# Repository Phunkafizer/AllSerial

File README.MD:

# AllSerial
## An universal sophisticated USB-serial converter

SEE PROJECTHOMEPAGE UNDER [https://www.seegel-systeme.de/2025/07/10/allserial](https://www.seegel-systeme.de/2025/07/10/allserial)

Over the course of time I had to work with many different devices which had to be connected via a kind of serial interface. There are lots of different cheap USB-serial adapters available, but no adapter was including all features I needed in a single device. Every USB-serial adapter has in common the USB Controller. So I came up with the idea having a masterboard providing all the common features like USB interface, isolation and diagnostic elements. The most used interfaces (RS232, RS485, TTL UART, TTY current loop & LIN) are build up on slave modules which can be plugged into the mainboard. If a custom interface is needed, there is an KiCad library available making it easy to create one by yourself. 

## Features
- Open source
- Isolated
- Reset button for reenumerating device on the USB
- Status LEDs (RX, TX, Power, TXEN)
- modular, just exchange daughterboard for different interfaces
- RS232 completley connected (RXD, TXD, RTS, CTS, DTR, DSR, RI, DCD)
- RS485, RS422 with Handshake
- TTY current loop 4/3/2 wire active/passive
- LIN
- TTL 1.8/2.5/3.3/5 V
- KiCad library for easily creating custom modules

## Modules (tested & working)
* Mainboard FT232

* RS 422/485 

* RS 232 

* TTL 

* TTY current loop 

* LIN 

* 1wire (with DS2480B) 

* Programmer for ESP8266 (auto reset&boot) 

## Modules (under development)
* Mainboard with ESP32-S3 for accessing slave modules via USB, WiFi & Bluetooth 

* mBus master
* Digi XBee radiomodem 

* eBus 

## Software
* [hterm](http://www.der-hammer.info/terminal/) (windows)
* [putty](https://www.chiark.greenend.org.uk/~sgtatham/putty/latest.html) (windows/unix)

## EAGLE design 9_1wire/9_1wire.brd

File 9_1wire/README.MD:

# 9 1wire
provides a 1-wire interface

* using IC DS2480B
* provides 12 V for programming 1wire eeproms

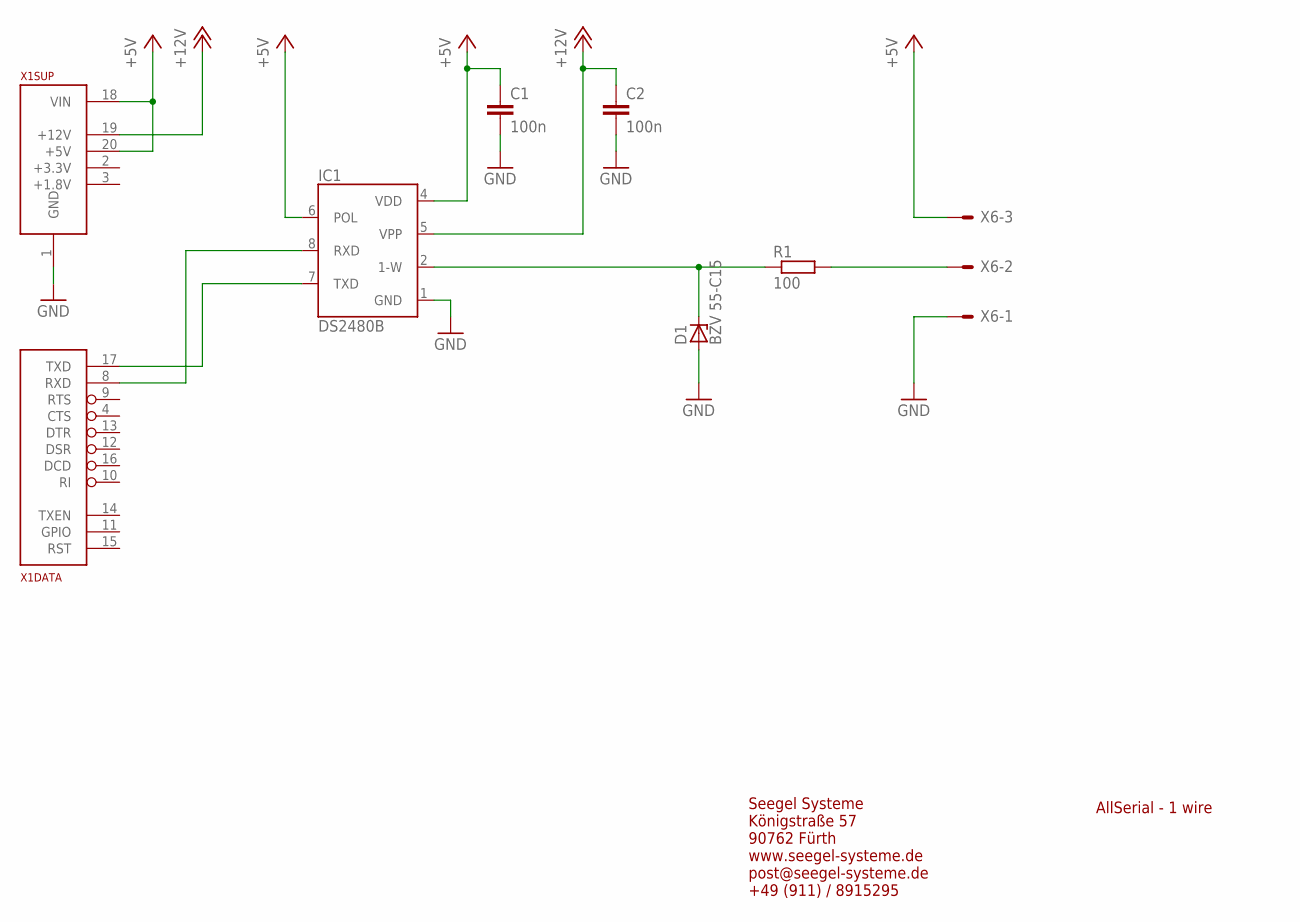
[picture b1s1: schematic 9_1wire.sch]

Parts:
C1, C2: 100n; C0805
D1: BZV 55-C15; SOD80C
IC1: DS2480B; SO08
R1: 100; R0805
X1: ALLSERIALSLAVE; DAUGHTER-THT
X6: AKL18X-03W; AKL182-03

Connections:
+5V: C1.1, IC1.4 (VDD), IC1.6 (POL), X1.18 (VIN), X1.20 (+5V), X6.P$3
+12V: C2.1, IC1.5 (VPP), X1.19 (+12V)
GND: C1.2, C2.2, D1.A, IC1.1 (GND), X1.1 (GND), X6.P$1
unnamed: IC1.7 (TXD), X1.17 (TXD)
unnamed: IC1.8 (RXD), X1.8 (RXD)
unnamed: D1.C, IC1.2 (1-W), R1.1
unnamed: R1.2, X6.P$2

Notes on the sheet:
AllSerial - 1 wire
Seegel Systeme Königstraße 57 90762 Fürth www.seegel-systeme.de post@seegel-systeme.de +49 (911) / 8915295

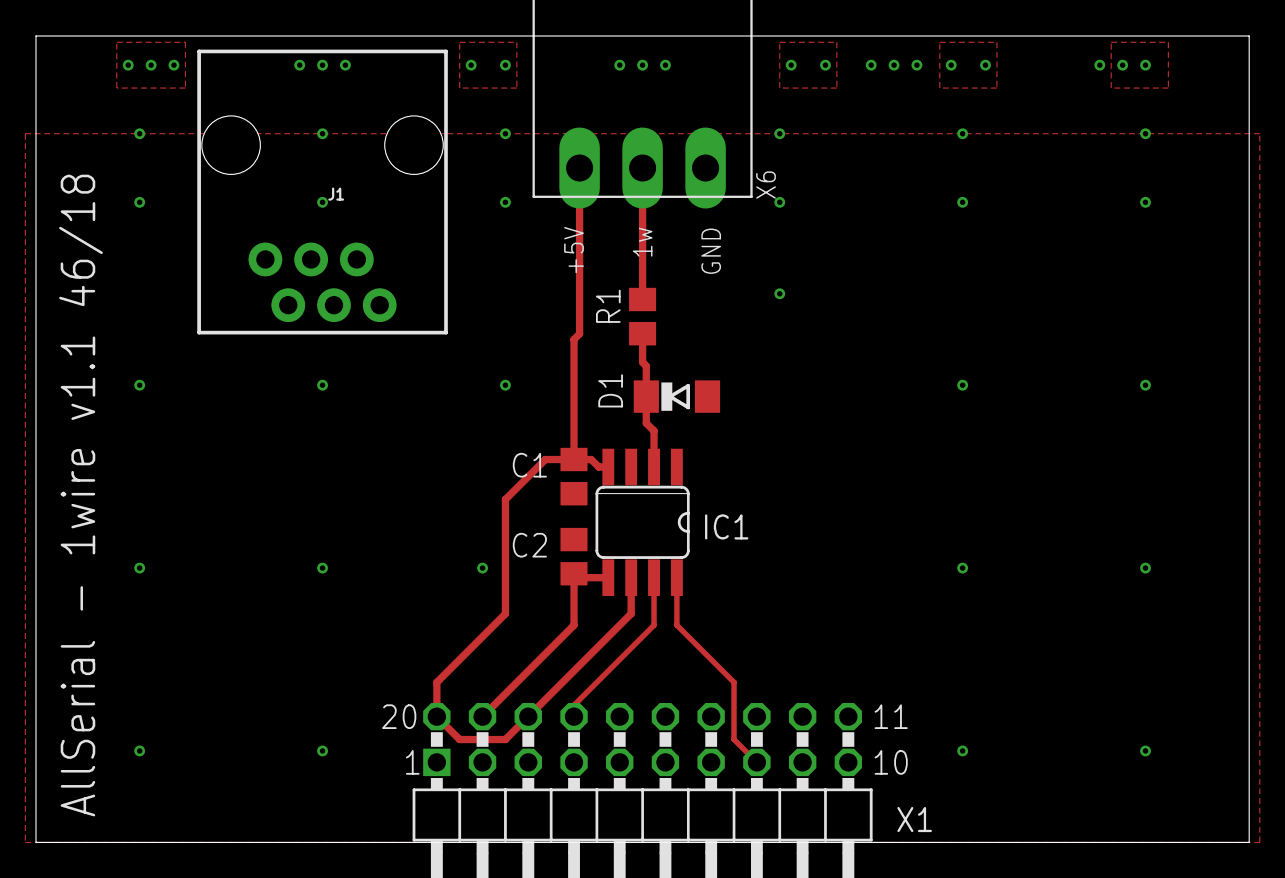
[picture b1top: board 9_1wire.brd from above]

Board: 2 copper layers, 67.4 x 44.8 mm, 8 parts (0 on the bottom side), 7 nets.

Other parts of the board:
J1: RJ11; RJ11-6

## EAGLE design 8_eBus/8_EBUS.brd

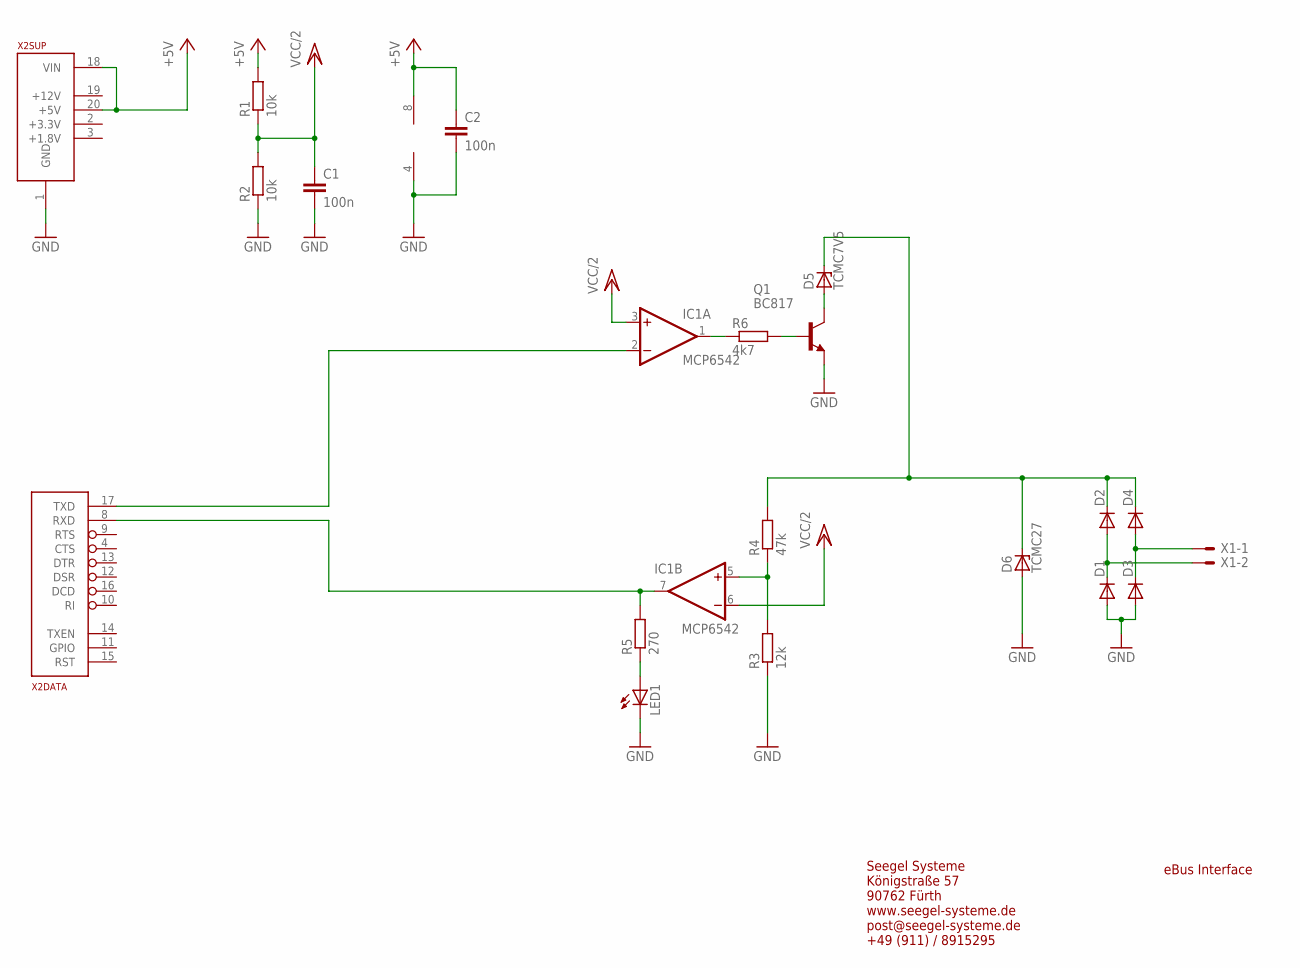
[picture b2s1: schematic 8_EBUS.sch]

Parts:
C1, C2: 100n; C0805
D1, D2, D3, D4: DIODE-SOD80C; SOD80C
D5: TCMC7V5; SOD80C
D6: TCMC27; SOD80C
IC1: MCP6542; SO08
LED1: LEDCHIPLED_0805; CHIPLED_0805
Q1: BC817; SOT23-BEC
R1, R2: 10k; R0805
R3: 12k; R0805
R4: 47k; R0805
R5: 270; R0805
R6: 4k7; R0805
X1: AKL18X-02W; AKL182-02
X2: ALLSERIALSLAVE; DAUGHTER-THT

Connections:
+5V: C2.1, IC1.8 (V+), R1.2, X2.18 (VIN), X2.20 (+5V)
GND: C1.2, C2.2, D1.A, D3.A, D6.A, IC1.4 (V-), LED1.C, Q1.E, R2.1, R3.1, X2.1 (GND)
unnamed: D2.C, D4.C, D5.C, D6.C, R4.2
unnamed: D3.C, D4.A, X1.P$1
unnamed: D1.C, D2.A, X1.P$2
unnamed: Q1.B, R6.2
unnamed: D5.A, Q1.C
unnamed: IC1.5 (+IN), R3.2, R4.1
unnamed: IC1.2 (-IN), X2.17 (TXD)
unnamed: IC1.1 (OUT), R6.1
unnamed: LED1.A, R5.1
unnamed: IC1.7 (OUT), R5.2, X2.8 (RXD)
VCC/2: C1.1, IC1.3 (+IN), IC1.6 (-IN), R1.1, R2.2

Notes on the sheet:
eBus Interface
Seegel Systeme Königstraße 57 90762 Fürth www.seegel-systeme.de post@seegel-systeme.de +49 (911) / 8915295

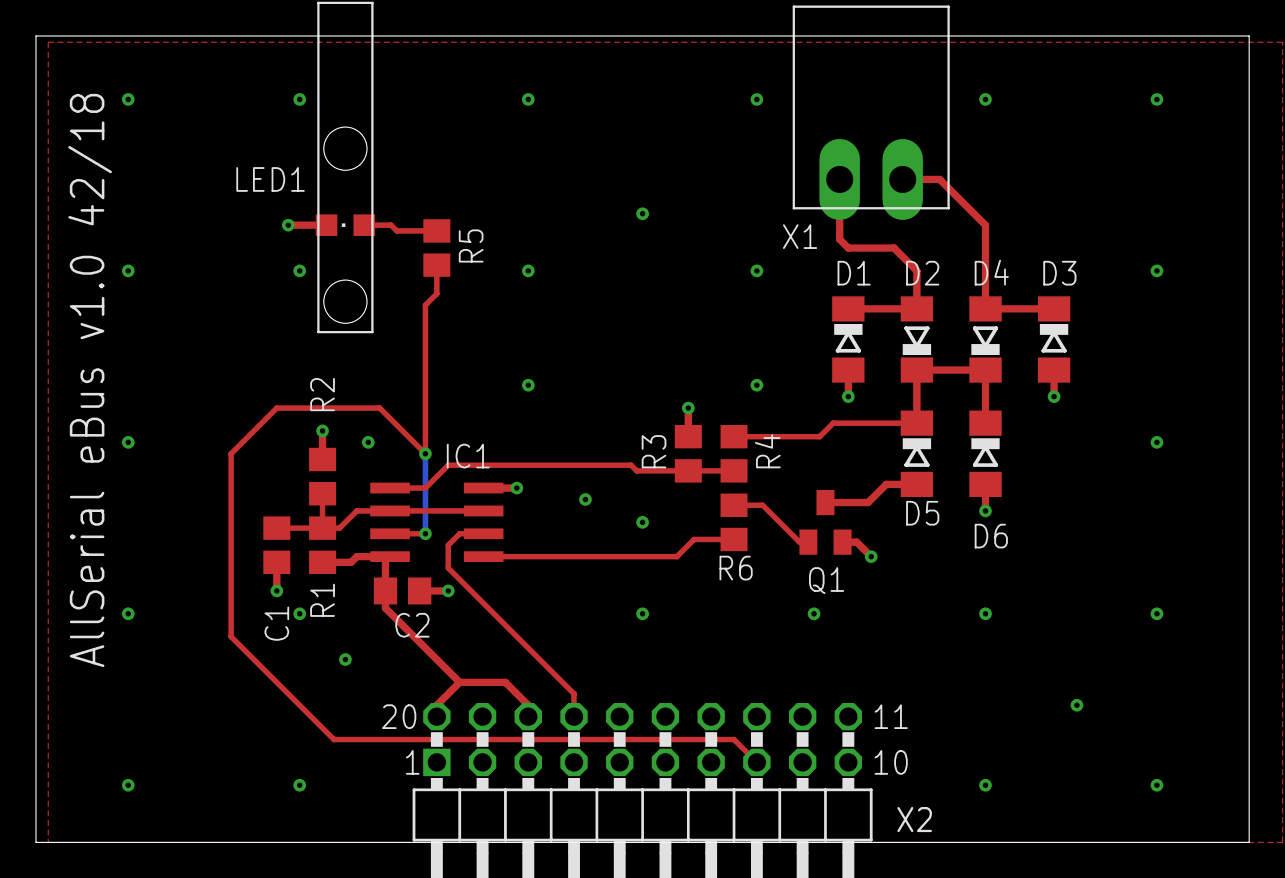
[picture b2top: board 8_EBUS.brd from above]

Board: 2 copper layers, 67.4 x 44.8 mm, 20 parts (0 on the bottom side), 13 nets.

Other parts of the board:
U$1: 1271.1000

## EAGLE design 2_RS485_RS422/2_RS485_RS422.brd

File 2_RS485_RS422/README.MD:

# AllSerial RS 422/485 module
Provides a RS 485/422 interface

* Jumper for termination
* Additional doublepair for RS422 with handshake lines
* RTS/DTR CTS/DSR for handshake can be select with jumper

Reichelt Warenkorb: https://www.reichelt.de/my/1489968

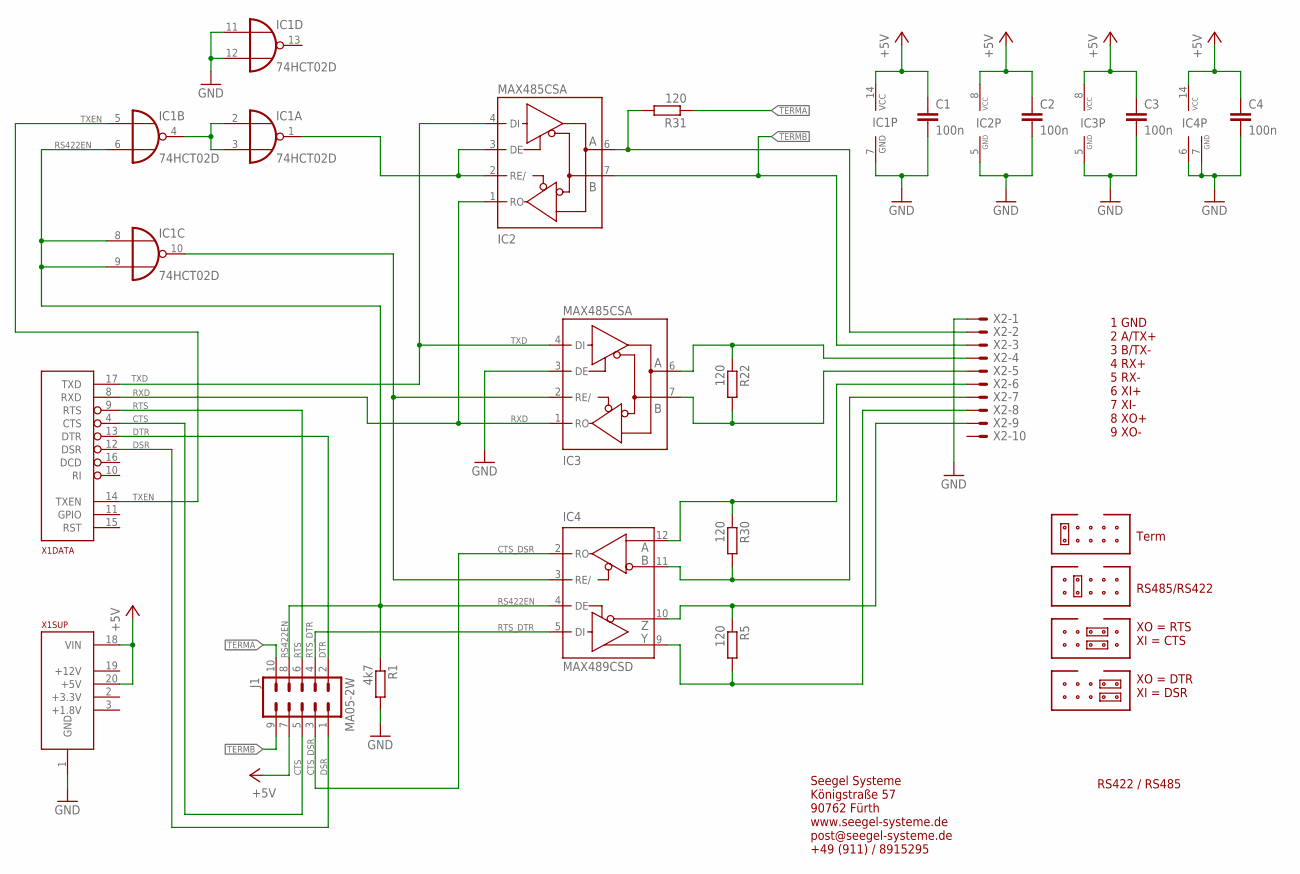
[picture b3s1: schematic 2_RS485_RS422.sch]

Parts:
C1, C2, C3, C4: 100n; C0805
IC1: 74HCT02D; SO14
IC2, IC3: MAX485CSA; SO08
IC4: MAX489CSD; SO14
J1: MA05-2W
R1: 4k7; R0805
R5, R22, R30, R31: 120; R0805
X1: ALLSERIALSLAVE; DAUGHTER-THT
X2: AKL18X-10W; AKL182-10

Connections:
+5V: C1.1, C2.1, C3.1, C4.1, IC1.14 (VCC), IC2.8 (VCC), IC3.8 (VCC), IC4.14 (VCC), J1.7, X1.18 (VIN), X1.20 (+5V)
CTS: J1.5, X1.4 (CTS)
CTS_DSR: IC4.2 (RO), J1.3
DSR: J1.1, X1.12 (DSR)
DTR: J1.2, X1.13 (DTR)
GND: C1.2, C2.2, C3.2, C4.2, IC1.7 (GND), IC1.11 (I0), IC1.12 (I1), IC2.5 (GND), IC3.3 (DE), IC3.5 (GND), IC4.6 (GND), IC4.7 (GND), R1.2, X1.1 (GND), X2.P$1
unnamed: IC4.11 (B), R30.2, X2.P$7
unnamed: IC4.10 (Z), R5.1, X2.P$9
unnamed: IC2.6 (A), R31.2, X2.P$2
unnamed: IC4.9 (Y), R5.2, X2.P$8
unnamed: IC4.12 (A), R30.1, X2.P$6
unnamed: IC3.7 (B), R22.2, X2.P$5
unnamed: IC3.6 (A), R22.1, X2.P$4
unnamed: IC1.2 (I0), IC1.3 (I1), IC1.4 (O)
unnamed: IC1.1 (O), IC2.2 (RE/), IC2.3 (DE)
unnamed: IC1.10 (O), IC3.2 (RE/), IC4.3 (RE/)
RS422EN: IC1.6 (I1), IC1.8 (I0), IC1.9 (I1), IC4.4 (DE), J1.8, R1.1
RTS: J1.6, X1.9 (RTS)
RTS_DTR: IC4.5 (DI), J1.4
RXD: IC2.1 (RO), IC3.1 (RO), X1.8 (RXD)
TERMA: J1.10, R31.1
TERMB: IC2.7 (B), J1.9, X2.P$3
TXD: IC2.4 (DI), IC3.4 (DI), X1.17 (TXD)
TXEN: IC1.5 (I0), X1.14 (TXEN)

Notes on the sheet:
Seegel Systeme Königstraße 57 90762 Fürth www.seegel-systeme.de post@seegel-systeme.de +49 (911) / 8915295
RS422 / RS485
Term
RS485/RS422
XO = RTS XI = CTS
XO = DTR XI = DSR
1 GND 2 A/TX+ 3 B/TX- 4 RX+ 5 RX- 6 XI+ 7 XI- 8 XO+ 9 XO-

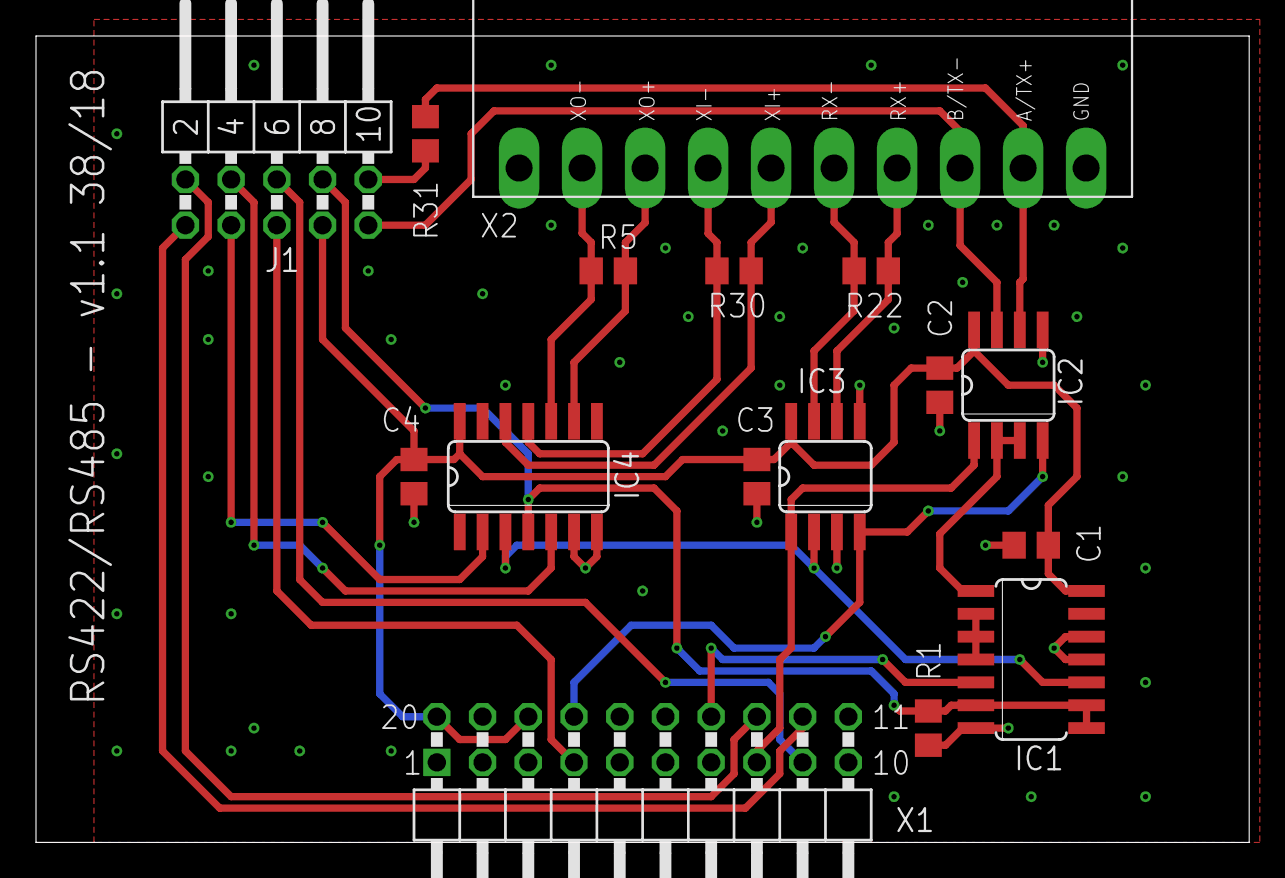
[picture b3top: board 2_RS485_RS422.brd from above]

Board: 2 copper layers, 67.4 x 44.8 mm, 18 parts (0 on the bottom side), 24 nets.

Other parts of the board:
U$4, U$5: JUMPER

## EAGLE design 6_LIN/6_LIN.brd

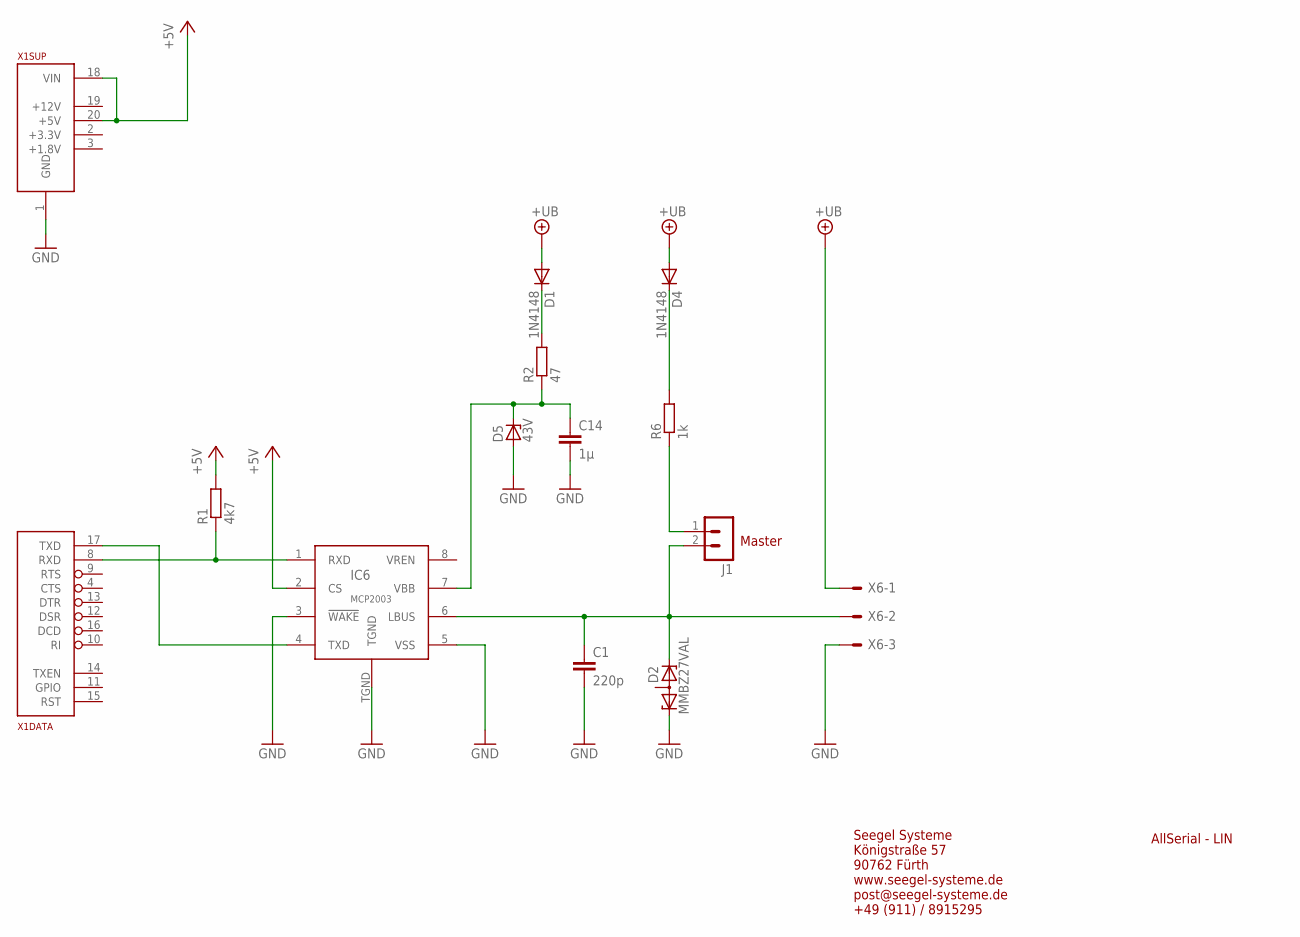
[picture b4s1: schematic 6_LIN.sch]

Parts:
C1: 220p; C0805
C14: 1µ; C0805
D1, D4: 1N4148; MINIMELF
D2: MMBZ27VAL; SOT23
D5: 43V; SOD80C
IC6: MCP2003; SOIC8T
J1: MA02-1W; MA02-W
R1: 4k7; R0805
R2: 47; R0805
R6: 1k; R0805
X1: ALLSERIALSLAVE; DAUGHTER-THT
X6: AKL18X-03W; AKL182-03

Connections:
+5V: IC6.2 (CS), R1.2, X1.18 (VIN), X1.20 (+5V)
+UB: D1.A, D4.A, X6.P$1
GND: C1.2, C14.2, D2.1 (K1), D5.A, IC6.3 (!WAKE), IC6.5 (VSS), IC6.TGND, X1.1 (GND), X6.P$3
unnamed: D1.C, R2.2
unnamed: D4.C, R6.2
unnamed: C14.1, D5.C, IC6.7 (VBB), R2.1
unnamed: C1.1, D2.2 (K2), IC6.6 (LBUS), J1.2, X6.P$2
unnamed: J1.1, R6.1
unnamed: IC6.4 (TXD), X1.17 (TXD)
unnamed: IC6.1 (RXD), R1.1, X1.8 (RXD)

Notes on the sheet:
AllSerial - LIN
Master
Seegel Systeme Königstraße 57 90762 Fürth www.seegel-systeme.de post@seegel-systeme.de +49 (911) / 8915295

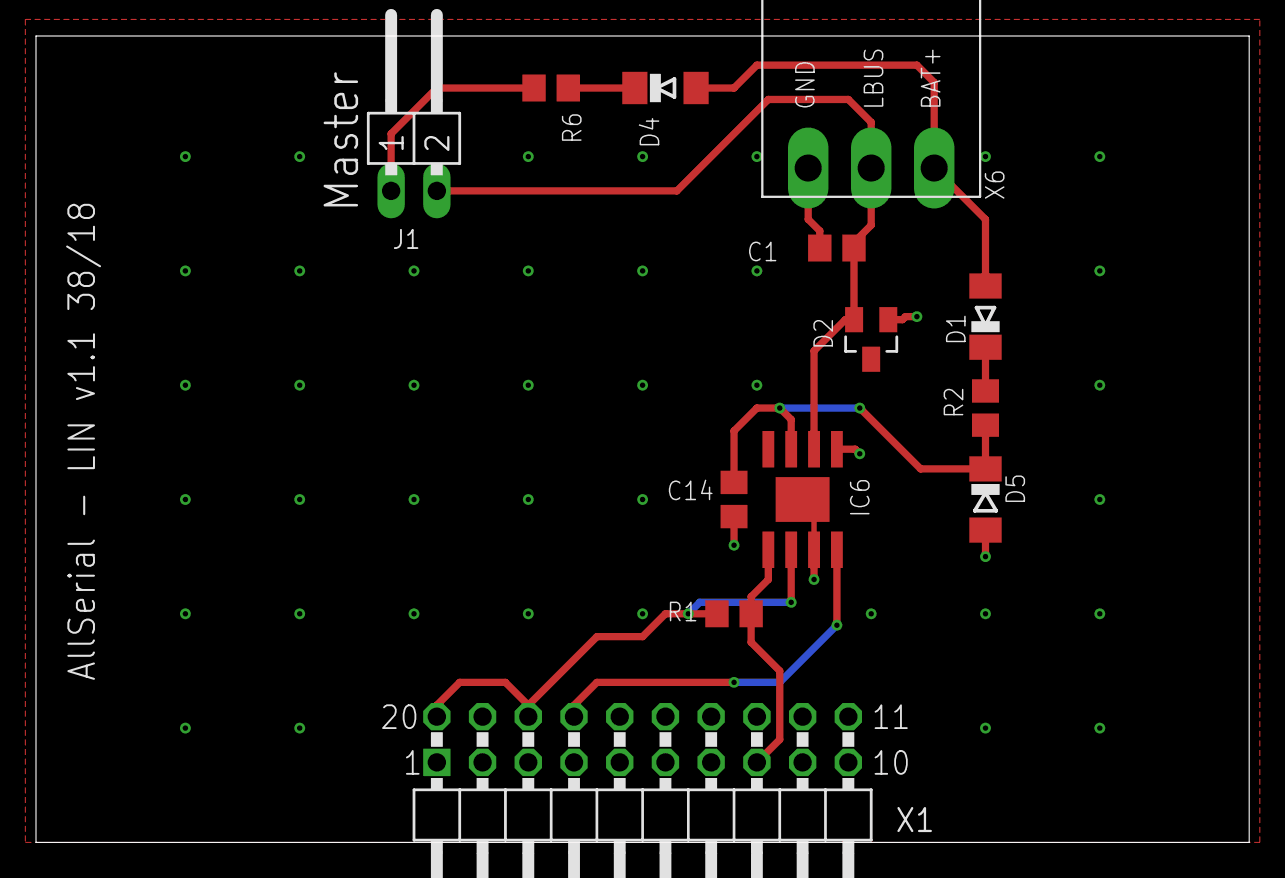
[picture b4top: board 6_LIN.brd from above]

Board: 2 copper layers, 67.4 x 44.8 mm, 13 parts (0 on the bottom side), 10 nets.

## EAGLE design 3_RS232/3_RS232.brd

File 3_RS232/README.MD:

# RS232
Provides a RS 422 interface (DTE)

* fully connected (TX, RX, RTS, CTS, DTR, DSR, RI, DCD)
* 9 pin D-SUB male connector

Reichelt Warenkorb: https://www.reichelt.de/my/1490023

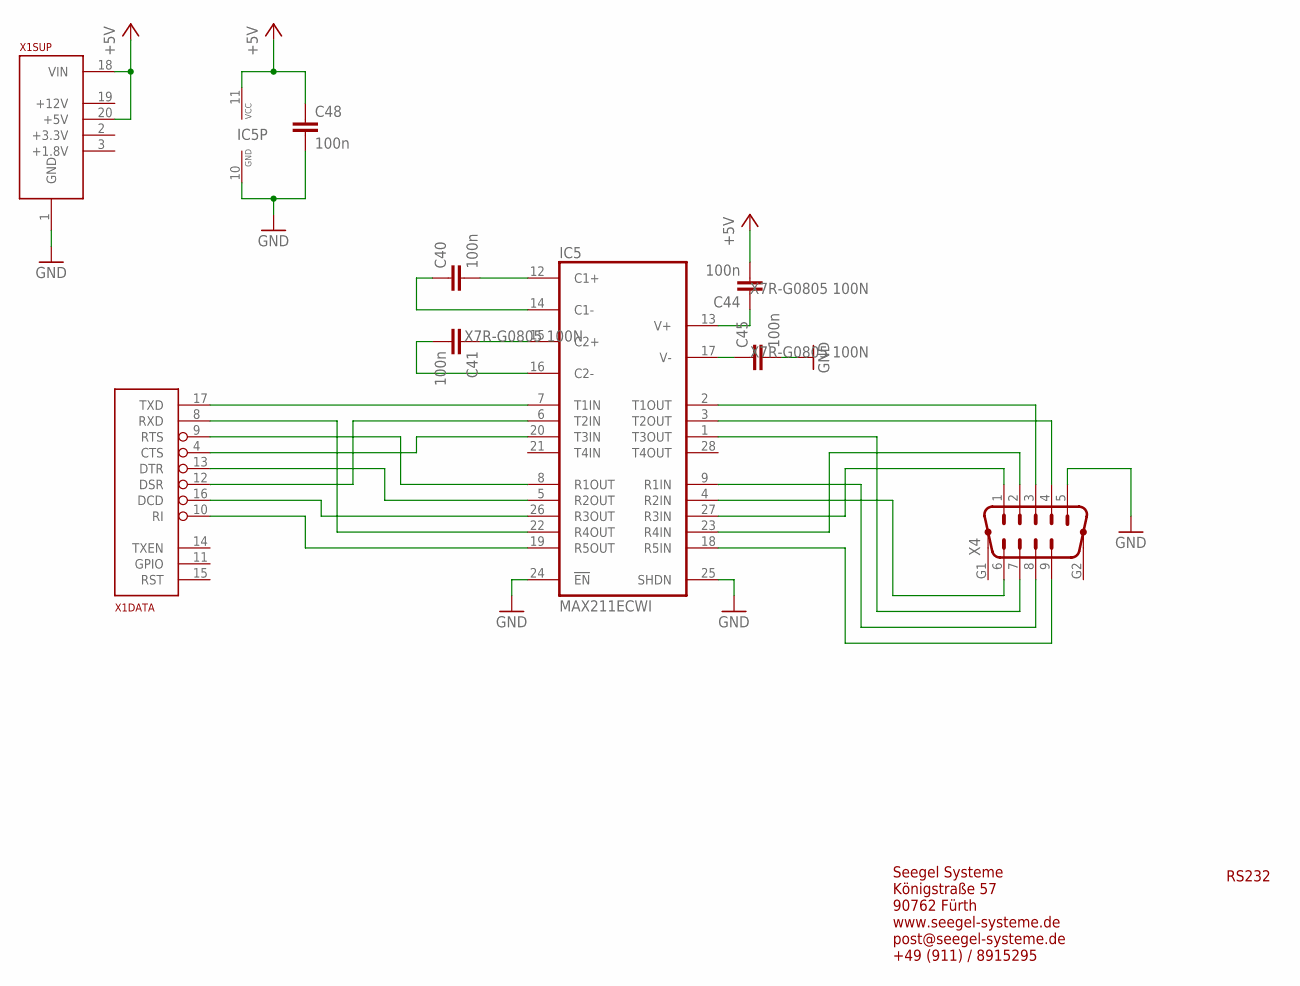
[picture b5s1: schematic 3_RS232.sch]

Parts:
C40, C41, C44, C45, C48: 100n; C0805
IC5: MAX211ECWI; SO28L
X1: ALLSERIALSLAVE; DAUGHTER-THT
X4: M09HP

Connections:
+5V: C44.2, C48.1, IC5.11 (VCC), X1.18 (VIN), X1.20 (+5V)
GND: C45.2, C48.2, IC5.10 (GND), IC5.24 (EN), IC5.25 (SHDN), X1.1 (GND), X4.5
unnamed: IC5.18 (R5IN), X4.9
unnamed: IC5.9 (R1IN), X4.8
unnamed: IC5.1 (T3OUT), X4.7
unnamed: IC5.4 (R2IN), X4.6
unnamed: IC5.27 (R3IN), X4.1
unnamed: IC5.23 (R4IN), X4.2
unnamed: IC5.2 (T1OUT), X4.3
unnamed: IC5.3 (T2OUT), X4.4
unnamed: C40.2, IC5.12 (C1+)
unnamed: C40.1, IC5.14 (C1-)
unnamed: C41.1, IC5.15 (C2+)
unnamed: C45.1, IC5.17 (V-)
unnamed: C44.1, IC5.13 (V+)
unnamed: C41.2, IC5.16 (C2-)
unnamed: IC5.7 (T1IN), X1.17 (TXD)
unnamed: IC5.22 (R4OUT), X1.8 (RXD)
unnamed: IC5.20 (T3IN), X1.4 (CTS)
unnamed: IC5.8 (R1OUT), X1.9 (RTS)
unnamed: IC5.26 (R3OUT), X1.16 (DCD)
unnamed: IC5.19 (R5OUT), X1.10 (RI)
unnamed: IC5.5 (R2OUT), X1.13 (DTR)
unnamed: IC5.6 (T2IN), X1.12 (DSR)

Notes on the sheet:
RS232
Seegel Systeme Königstraße 57 90762 Fürth www.seegel-systeme.de post@seegel-systeme.de +49 (911) / 8915295

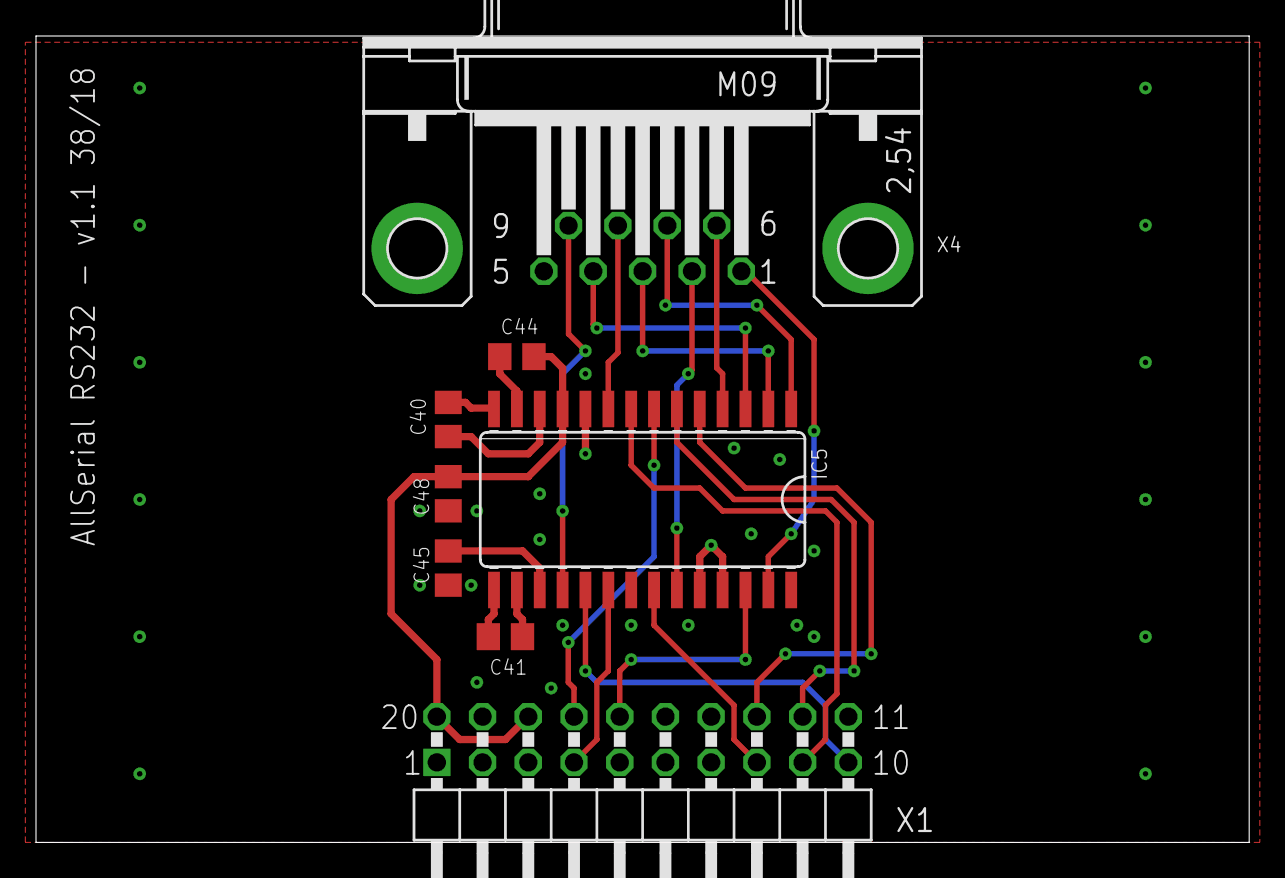
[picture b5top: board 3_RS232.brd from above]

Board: 2 copper layers, 67.4 x 44.8 mm, 8 parts (0 on the bottom side), 24 nets.

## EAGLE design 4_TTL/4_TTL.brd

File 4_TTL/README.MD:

# TTL connector
The TTL connector module provides all UART pins on a 3.5 mm screwclamp

* Full connection: TXD, RXD, CTS, RTS, DTR, DSR, DCD, RI
* Selectable voltage 5 V, 3.3 V, 2.5 V, 1.8 V, external

Reichelt Warenkorb: https://www.reichelt.de/my/1490024

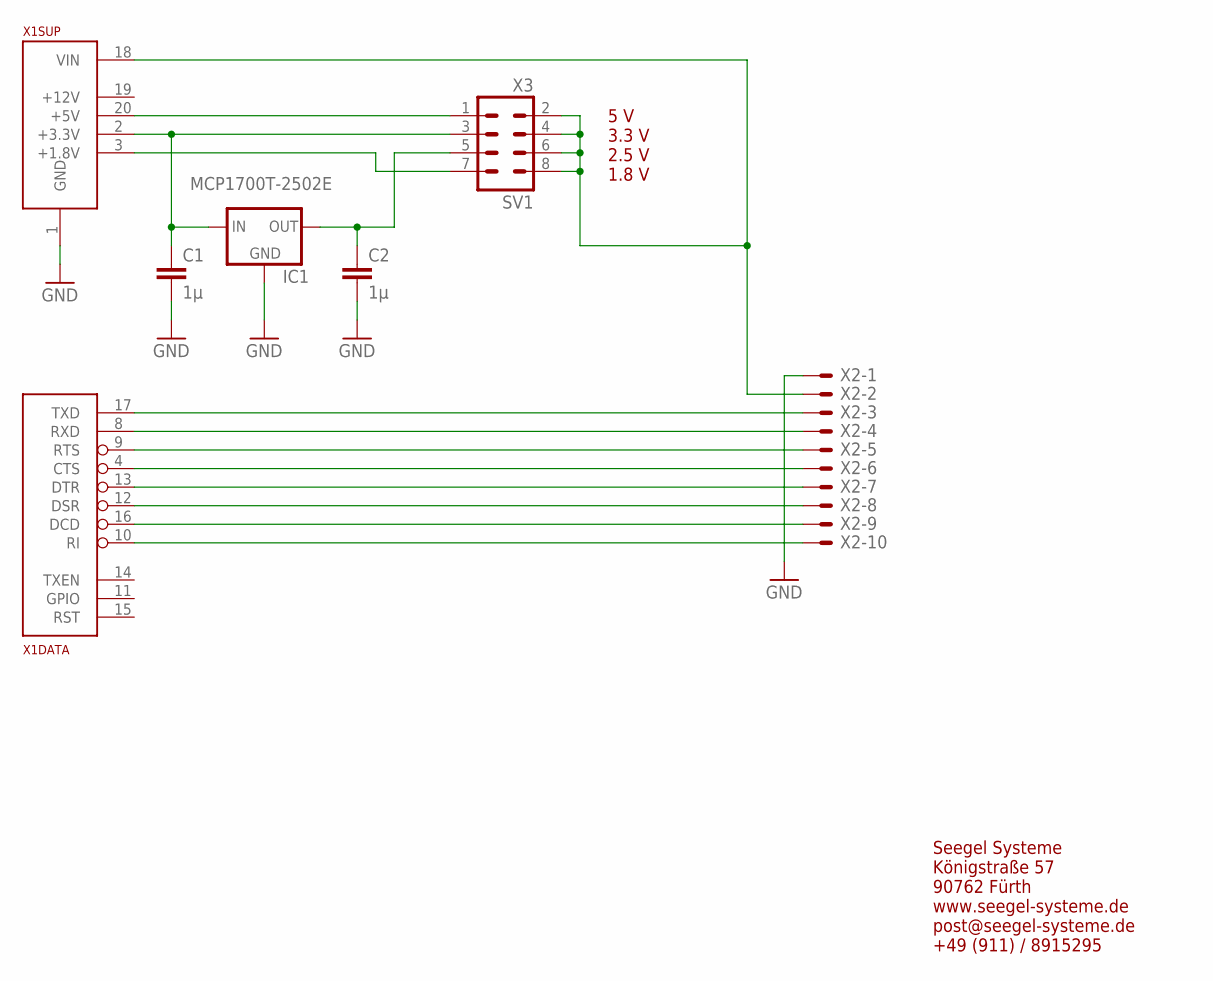
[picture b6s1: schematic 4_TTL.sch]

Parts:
C1, C2: 1µ; C0805K
IC1: MCP1700T-2502E; SOT23
SV1: X3; MA04-2W
X1: ALLSERIALSLAVE; DAUGHTER-THT
X2: AKL18X-10W; AKL182-10

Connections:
CTS4: X1.4 (CTS), X2.P$6
DCD4: X1.16 (DCD), X2.P$9
DSR4: X1.12 (DSR), X2.P$8
DTR4: X1.13 (DTR), X2.P$7
GND: C1.2, C2.2, IC1.1 (GND), X1.1 (GND), X2.P$1
unnamed: SV1.2, SV1.4, SV1.6, SV1.8, X1.18 (VIN), X2.P$2
unnamed: SV1.7, X1.3 (+1.8V)
unnamed: SV1.1, X1.20 (+5V)
unnamed: C1.1, IC1.3 (IN), SV1.3, X1.2 (+3.3V)
unnamed: C2.1, IC1.2 (OUT), SV1.5
RI4: X1.10 (RI), X2.P$10
RTS4: X1.9 (RTS), X2.P$5
RXD4: X1.8 (RXD), X2.P$4
TXD4: X1.17 (TXD), X2.P$3

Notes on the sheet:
5 V 3.3 V 2.5 V 1.8 V
Seegel Systeme Königstraße 57 90762 Fürth www.seegel-systeme.de post@seegel-systeme.de +49 (911) / 8915295

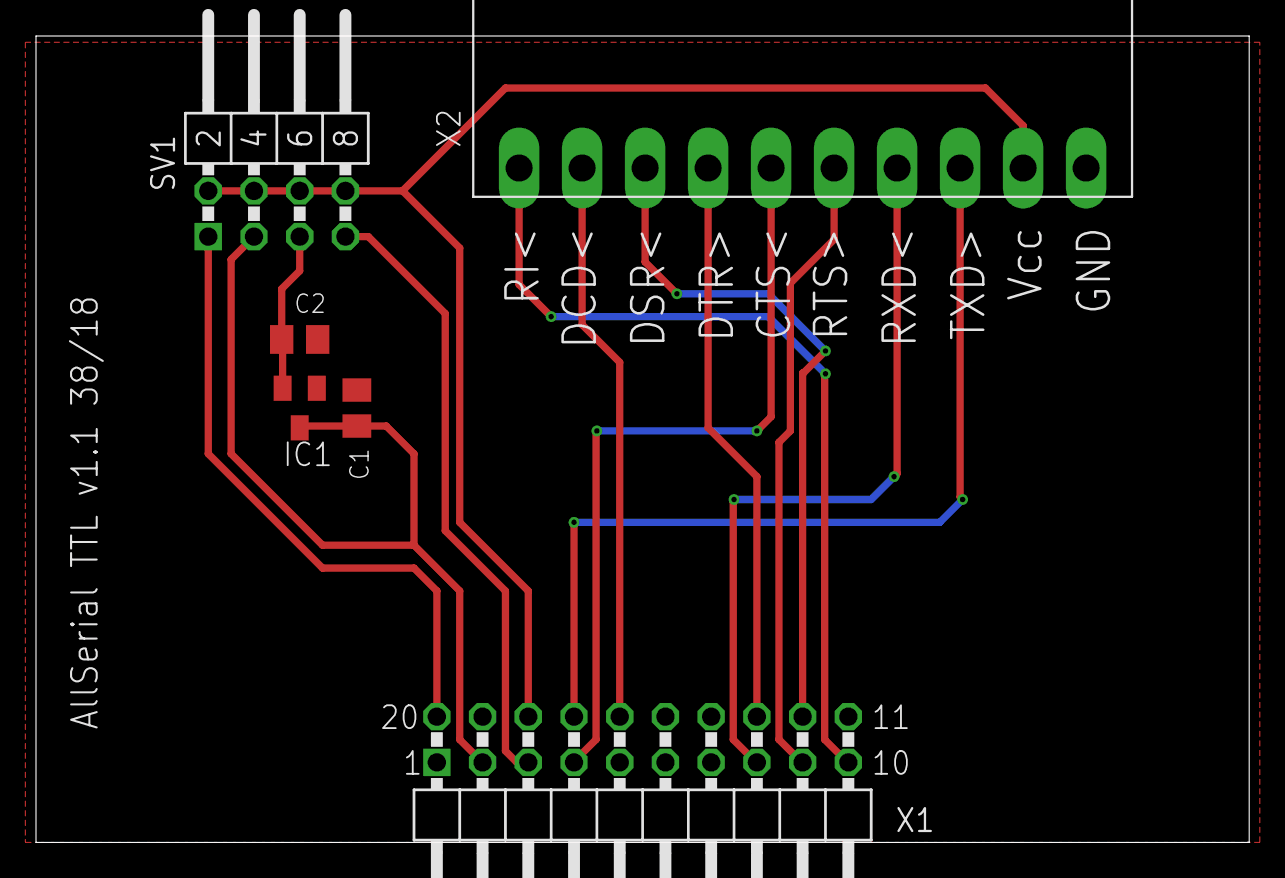
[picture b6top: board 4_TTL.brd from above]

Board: 2 copper layers, 67.4 x 44.8 mm, 6 parts (0 on the bottom side), 14 nets.

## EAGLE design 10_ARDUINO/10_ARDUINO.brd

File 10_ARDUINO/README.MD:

# 10 development board for Arduino Pro Mini

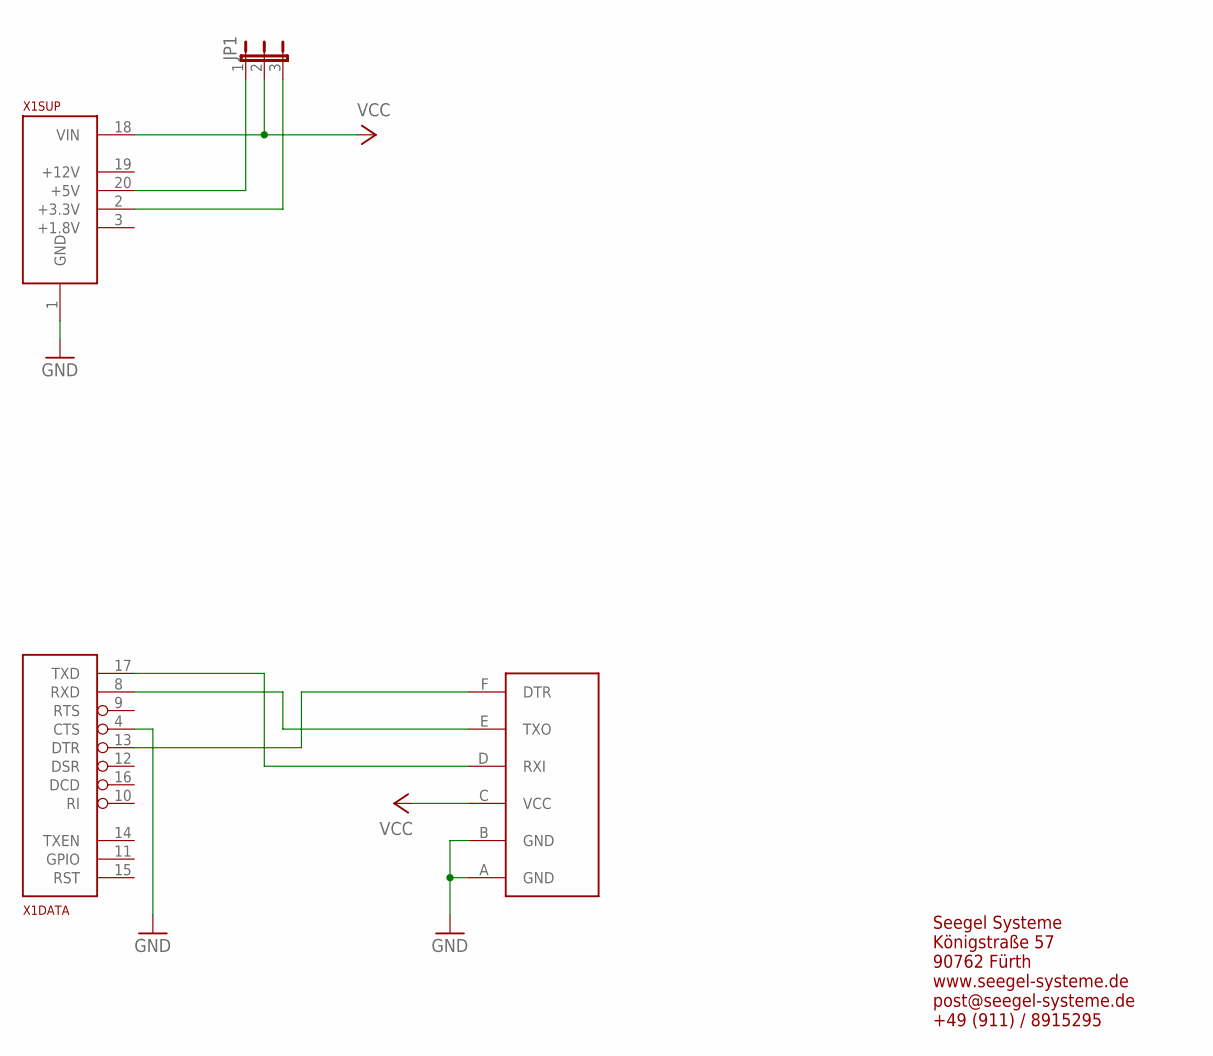
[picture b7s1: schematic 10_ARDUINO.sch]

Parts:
JP1: JP2E; JP2
M1: ARDUINO_PROMINI
X1: ALLSERIALSLAVE; DAUGHTER-THT

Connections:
GND: M1.A (GND), M1.B (GND), X1.1 (GND), X1.4 (CTS)
unnamed: M1.D (RXI), X1.17 (TXD)
unnamed: M1.E (TXO), X1.8 (RXD)
unnamed: M1.F (DTR), X1.13 (DTR)
unnamed: JP1.1, X1.20 (+5V)
unnamed: JP1.3, X1.2 (+3.3V)
VCC: JP1.2, M1.C (VCC), X1.18 (VIN)

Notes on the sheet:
Seegel Systeme Königstraße 57 90762 Fürth www.seegel-systeme.de post@seegel-systeme.de +49 (911) / 8915295

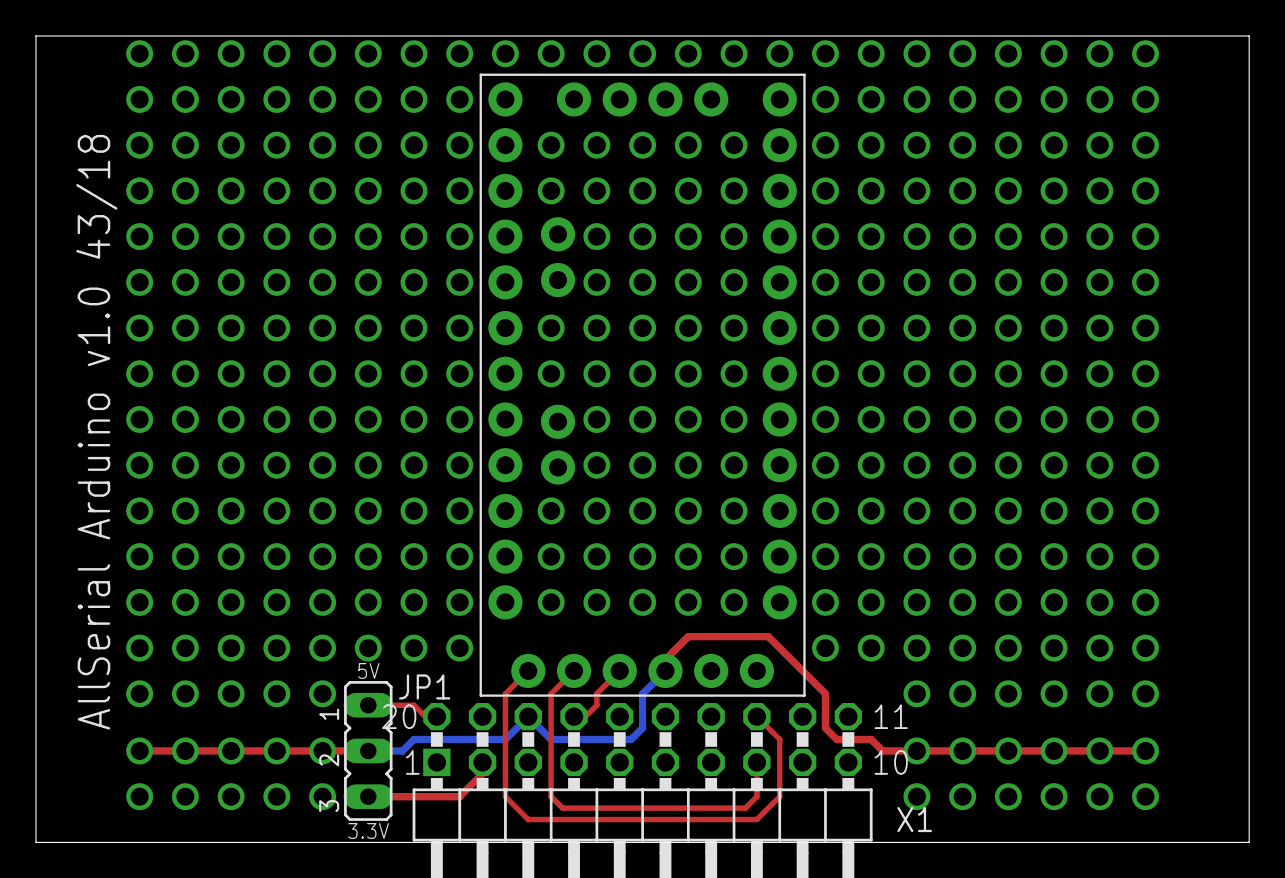
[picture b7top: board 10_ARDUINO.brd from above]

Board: 2 copper layers, 67.4 x 44.8 mm, 3 parts (0 on the bottom side), 7 nets.

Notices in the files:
parts and their libraries:
SparkFun-Connectors: Licensing: Creative Commons ShareAlike 4.0 International - https://creativecommons.org/licenses/by-sa/4.0
